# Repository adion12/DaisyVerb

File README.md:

# DaisyVerb
Reverb algorithms for the Daisy Seed

# Audio Samples
Mono and stereo audio samples of reverberators in action included. Audio files appended with a '1' demonstrate the Dry/Wet parameter, while those appended with a '2' demonstrate the feedback gain parameter.    
    
Source material of files appended with a...    
'1': [Round Midnight by Wes Montgomery](https://www.youtube.com/watch?v=PMhMiBxuqkg)   
'2': [Flash In The Pan by Against All Logic](https://www.youtube.com/watch?v=LaSEOVulOY0)   

# Important note
Code relies on the Daisy Seed's analog pins A0, A1, A2, and A3. The hardware set-up for each one is a potentiometer wiping between 3.3V and GND.

The dattorro and zita reverbs were written for development on the Versio platform. https://noiseengineering.us/pages/world-of-versio/ 

# Schematic & PCB
During the process of writing these reverb algorithms I made a simple dev board to avoid the troubles of working on a breadboard. The daisyboard.sch and daisyboard.brd are schematic and PCB files made in EAGLE. These were designed with consideration of certain PCB fabrication limitations at [The Hive Makerspace](https://hive.ece.gatech.edu), such as no through-hole plating.

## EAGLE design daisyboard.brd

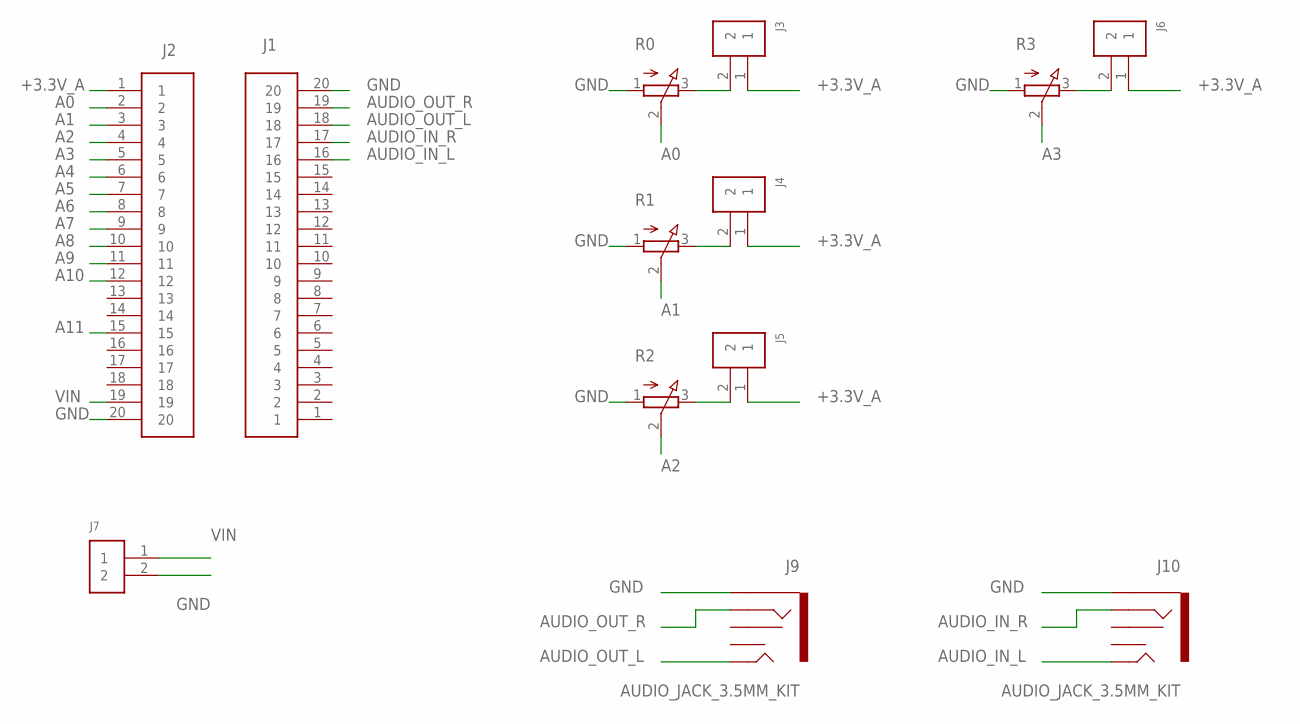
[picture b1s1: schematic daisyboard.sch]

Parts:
J1, J2: 61302011121
J3, J4, J5, J6, J7: 61300211121
J9, J10: AUDIO_JACK_3.5MM_KIT; AUDIO-JACK-KIT
R0, R1, R2, R3: 3RP/1610N

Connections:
+3.3V_A: J2.1, J3.1, J4.1, J5.1, J6.1
A0: J2.2, R0.2 (S)
A1: J2.3, R1.2 (S)
A2: J2.4, R2.2 (S)
A3: J2.5, R3.2 (S)
A4: J2.6
A5: J2.7
A6: J2.8
A7: J2.9
A8: J2.10
A9: J2.11
A10: J2.12
A11: J2.15
AUDIO_IN_L: J1.16, J10.TIP
AUDIO_IN_R: J1.17, J10.RING
AUDIO_OUT_L: J1.18, J9.TIP
AUDIO_OUT_R: J1.19, J9.RING
GND: J1.20, J2.20, J7.2, J9.SLEEVE, J10.SLEEVE, R0.1 (A), R1.1 (A), R2.1 (A), R3.1 (A)
unnamed: J3.2, R0.3 (E)
unnamed: J4.2, R1.3 (E)
unnamed: J5.2, R2.3 (E)
unnamed: J6.2, R3.3 (E)
VIN: J2.19, J7.1

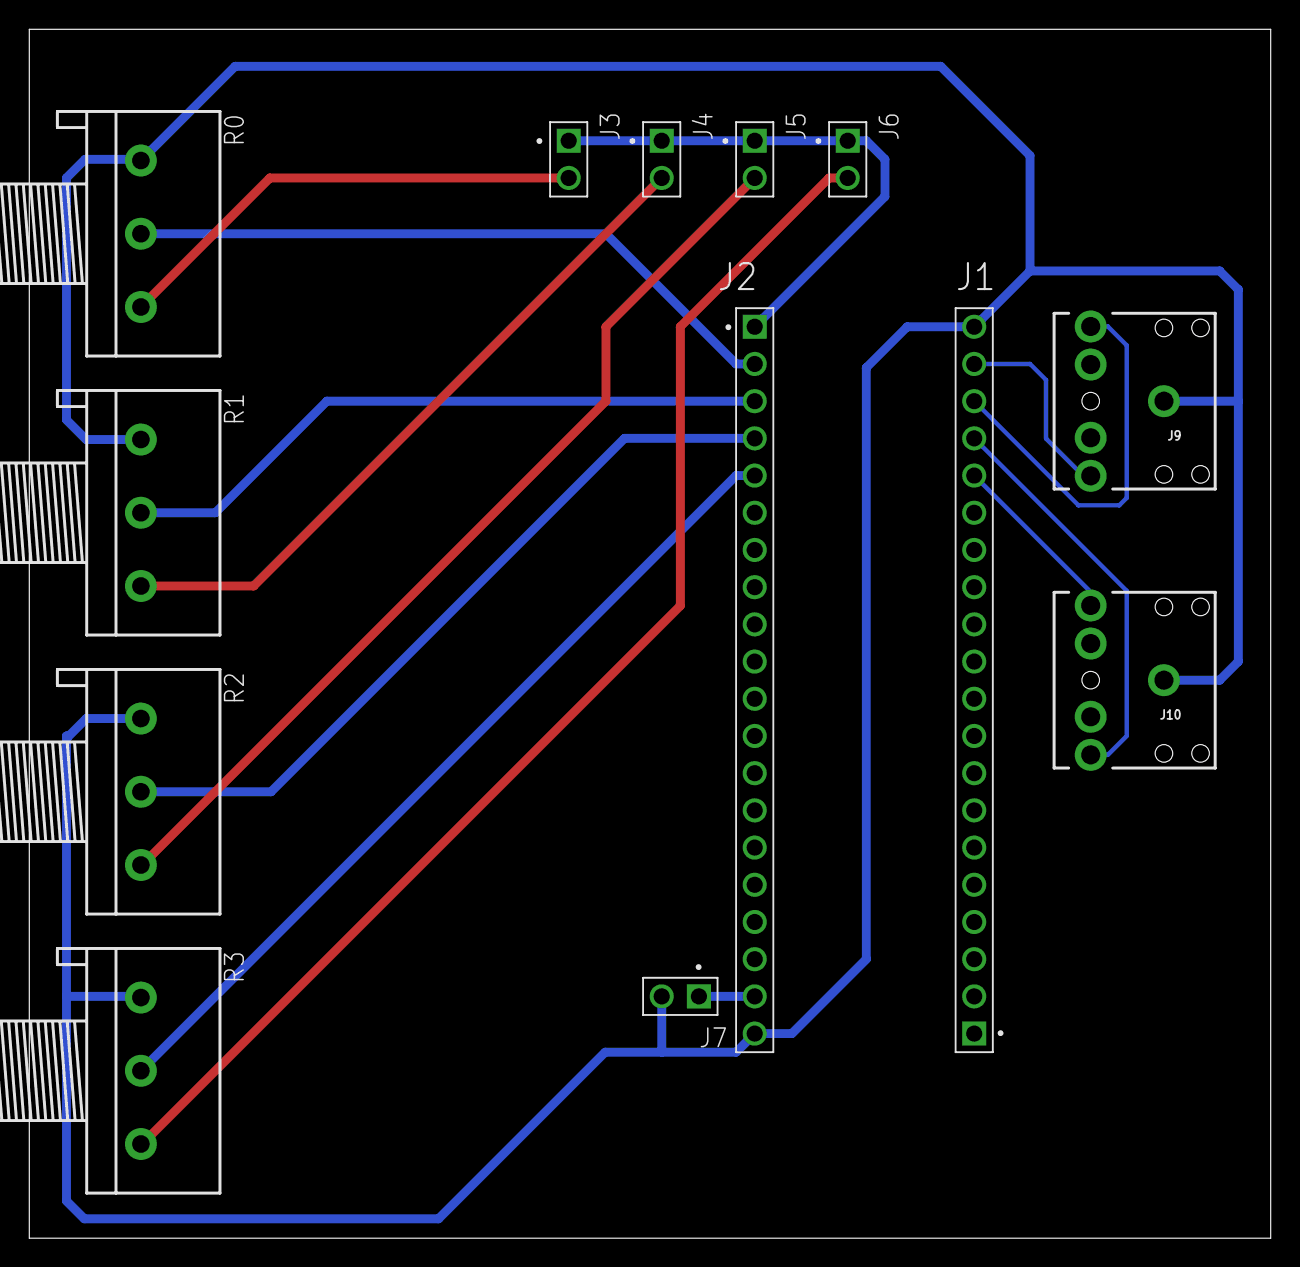
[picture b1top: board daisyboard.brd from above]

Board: 2 copper layers, 84.8 x 82.5 mm, 13 parts (0 on the bottom side), 15 nets.

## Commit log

2025-12-11 Rename myFreeverb_mono.cpp to freeverb_mono.cpp
2025-12-11 Rename myFreeverb_stereo.cpp to freeverb_stereo.cpp

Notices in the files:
parts and their libraries:
SparkFun-Connectors: Licensing: Creative Commons ShareAlike 4.0 International - https://creativecommons.org/licenses/by-sa/4.0
